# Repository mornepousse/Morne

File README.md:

The keyboard I created is a derivative of the Jorne and Kyria rev2, two keyboards highly appreciated in the community of mechanical keyboard enthusiasts. I took the best for me.

fr : Le clavier que j'ai créé est un dérivé du Jorne et du Kyria rev2, deux claviers très appréciés dans la communauté des amateurs de claviers mécaniques. J'ai pris le meilleur pour moi.

Update: 

Currently, I have not yet had the time to test the PCB and create the QMK code.

Actuellement, je n'ai pas encore eu le temps de tester le PCB et de créer le code QMK.

## PCB

Creation date: 02/12/2022

By ordering on [JLCPCB](https://cart.jlcpcb.com/quote?orderType=1&stencilLayer=2&stencilWidth=100&stencilLength=100&stencilCounts=5):

x 5 = 10.60$

u = 2.12$ x 2 = 4.24$

| Id | Reference | Package | Quantity | Designation | Supplier and ref | Ali price |
|----|-----------|---------|----------|------------|-------------------|------|
| 1  | D1,D2,D3...| Diode_TH_SOD123EKR | 26 | D |  [aliexpress](https://fr.aliexpress.com/item/1005003631407506.html?spm=a2g0o.order_list.order_list_main.10.6f255e5bMe6RnY&gatewayAdapt=glo2fra) , [TME](https://www.tme.eu/fr/details/1n5711w-7-f/diodes-schottky-smd/diodes-incorporated/) | 0.0546€ x 26 = 1.42€ |
| 2  | L1,L2,L3...| SK6812MINI_rev | 26 | SK6812MINI |  [aliexpress](https://fr.aliexpress.com/item/1005003021596311.html?spm=a2g0o.order_list.order_list_main.20.6f255e5bMe6RnY&gatewayAdapt=glo2fra) | 0.0704€ x 26 = 1.83€ |
| 3  | SW1,SW2,SW3...| MX_Socket_18mm | 26 | SW_PUSH | [aliexpress](https://fr.aliexpress.com/item/1005003873653184.html?spm=a2g0o.order_list.order_list_main.55.6f255e5bMe6RnY&gatewayAdapt=glo2fra)  | 0.1285€ x 26 = 3.34€ |
| 5  | U1 | ProMicro_v2 | 1 | ProMicro | [aliexpress](https://fr.aliexpress.com/item/1005003622414316.html?spm=a2g0o.order_list.order_list_main.26.6f255e5bMe6RnY&gatewayAdapt=glo2fra)  | 6.155€ |
| 8  | JP1 | JPC2 | 1 |  1X4Pin | [aliexpress](https://fr.aliexpress.com/item/4000979967513.html?spm=a2g0o.productlist.main.15.5b3f66e9o9m0cy&algo_pvid=850782ff-bfc7-4801-b06f-c64a524add1d&algo_exp_id=850782ff-bfc7-4801-b06f-c64a524add1d-7&pdp_ext_f=%7B%22sku_id%22%3A%2210000013144422246%22%7D&pdp_npi=3%40dis%21EUR%210.95%210.91%21%21%21%21%21%4021227e5116761981638552814d0652%2110000013144422246%21sea%21FR%212090266028&curPageLogUid=i54TIsZb6YSi)  | 0.182€ |
| 9  | J2 | OLED | 1 | OLED |  [aliexpress](https://fr.aliexpress.com/item/33024849277.html?spm=a2g0o.order_list.order_list_main.288.3e135e5bkwqkdx&gatewayAdapt=glo2fra) | 3.10€ |
| 10 | J1 | MJ-4PP-9 | 1 | MJ-4PP-9 |  [aliexpress](https://fr.aliexpress.com/item/33029465106.html?spm=a2g0o.order_list.order_list_main.253.3e135e5bkwqkdx&gatewayAdapt=glo2fra) | 0.246€ |
| 11 | RSW1 | ResetSW | 1 | SW_PUSH | [aliexpress](https://fr.aliexpress.com/item/1005004067514307.html?spm=a2g0o.productlist.main.1.73f16315tgnplA&algo_pvid=d4307642-89a4-423d-b78d-a7bb9a884aa8&algo_exp_id=d4307642-89a4-423d-b78d-a7bb9a884aa8-0&pdp_ext_f=%7B%22sku_id%22%3A%2212000027928467484%22%7D&pdp_npi=3%40dis%21EUR%210.52%210.46%21%21%21%21%21%40211bea0816761983658792786d0728%2112000027928467484%21sea%21FR%212090266028&curPageLogUid=7tFJg1Tj6lU0)  | 0.137€ |
| 12 | L22,L23,L24... | SK6812MINI_underglow_rev | 7 | SK6812MINI |  [aliexpress](https://fr.aliexpress.com/item/1005003021596311.html?spm=a2g0o.order_list.order_list_main.20.3e135e5bkwqkdx&gatewayAdapt=glo2fra) | 0.0704€ x 7 = 0.49€ |

Total price : 16.45€ x 2 = 32.90€

Other Parts:
| Name | links |
|------------------------|-----------------------------------------------|
| Jack TRRS cable | [ali1](https://fr.aliexpress.com/item/1005003415667083.html?spm=a2g0o.productlist.main.37.3441d84fbFu5Hf&algo_pvid=1adb3a47-ca94-434c-803d-4ccde599e237&algo_exp_id=1adb3a47-ca94-434c-803d-4ccde599e237-18&pdp_ext_f=%7B%22sku_id%22%3A%2212000025692890634%22%7D&pdp_npi=3%40dis%21EUR%212.14%211.81%21%21%21%21%21%4021227d8316762009574963433d0686%2112000025692890634%21sea%21FR%212090266028&curPageLogUid=nj2yMe0X7UII) [ali2](https://fr.aliexpress.com/item/33006667627.html?spm=a2g0o.productlist.main.25.3441d84fbFu5Hf&algo_pvid=db7c9240-7399-4f47-bad7-a78af453f498&algo_exp_id=db7c9240-7399-4f47-bad7-a78af453f498-12&pdp_ext_f=%7B%22sku_id%22%3A%2267037901505%22%7D&pdp_npi=3%40dis%21EUR%212.33%212.1%21%21%21%21%21%4021227e5116762010359954759d0652%2167037901505%21sea%21FR%212090266028&curPageLogUid=f0e0CcMaVshO) [ali3](https://fr.aliexpress.com/item/1005002888851426.html?spm=a2g0o.productlist.main.3.3441d84fbFu5Hf&algo_pvid=f9d24cf2-f17b-4ef0-a9a0-7f2f2ca77156&algo_exp_id=f9d24cf2-f17b-4ef0-a9a0-7f2f2ca77156-1&pdp_ext_f=%7B%22sku_id%22%3A%2212000022630947685%22%7D&pdp_npi=3%40dis%21EUR%213.8%212.66%21%21%21%21%21%40211bda9b16762013003935948d0706%2112000022630947685%21sea%21FR%212090266028&curPageLogUid=8BMH4jwvmLwd) |
| Switchs | [ali1](https://fr.aliexpress.com/item/1005003436102892.html?spm=a2g0o.order_list.order_list_main.223.34db5e5bkYd3Bk&gatewayAdapt=glo2fra), [ali Khail Cream](https://fr.aliexpress.com/item/1005003694230110.html?spm=a2g0o.productlist.main.1.5385245cS4FtLp&algo_pvid=043b18d1-9122-4b42-8289-2a2ee88619fe&algo_exp_id=043b18d1-9122-4b42-8289-2a2ee88619fe-0&pdp_ext_f=%7B%22sku_id%22%3A%2212000026831639163%22%7D&pdp_npi=3%40dis%21EUR%21177.39%2172.73%21%21%21%21%21%402102188b16762015218328204d070d%2112000026831639163%21sea%21FR%212090266028&curPageLogUid=lFpdV2qDqqbg) |
| Keycaps | [AF SA](https://fr.aliexpress.com/item/1005003935785708.html?spm=a2g0o.order_list.order_list_main.5.41db5e5b7Wn8vO&gatewayAdapt=glo2fra), [cerise](https://fr.aliexpress.com/item/1005003932690197.html?gatewayAdapt=glo2fra) |

Simulate the final price (case not included):

| PCB | SMDs | Switchs | Keycaps[?](https://fr.aliexpress.com/item/1005003935785708.html?spm=a2g0o.order_list.order_list_main.5.41db5e5b7Wn8vO&gatewayAdapt=glo2fra) | Total |
|----------|----------|----------|----------|----------|
| 3.97€ | 32.90€ | 18.06€ | 48.98€ | 103.91€ |

[BOM](https://github.com/mornepousse/Morne/blob/jorne/doc/BOM.md)

[Firmware](https://github.com/mornepousse/Rouge-Gorge_QMX_Part)

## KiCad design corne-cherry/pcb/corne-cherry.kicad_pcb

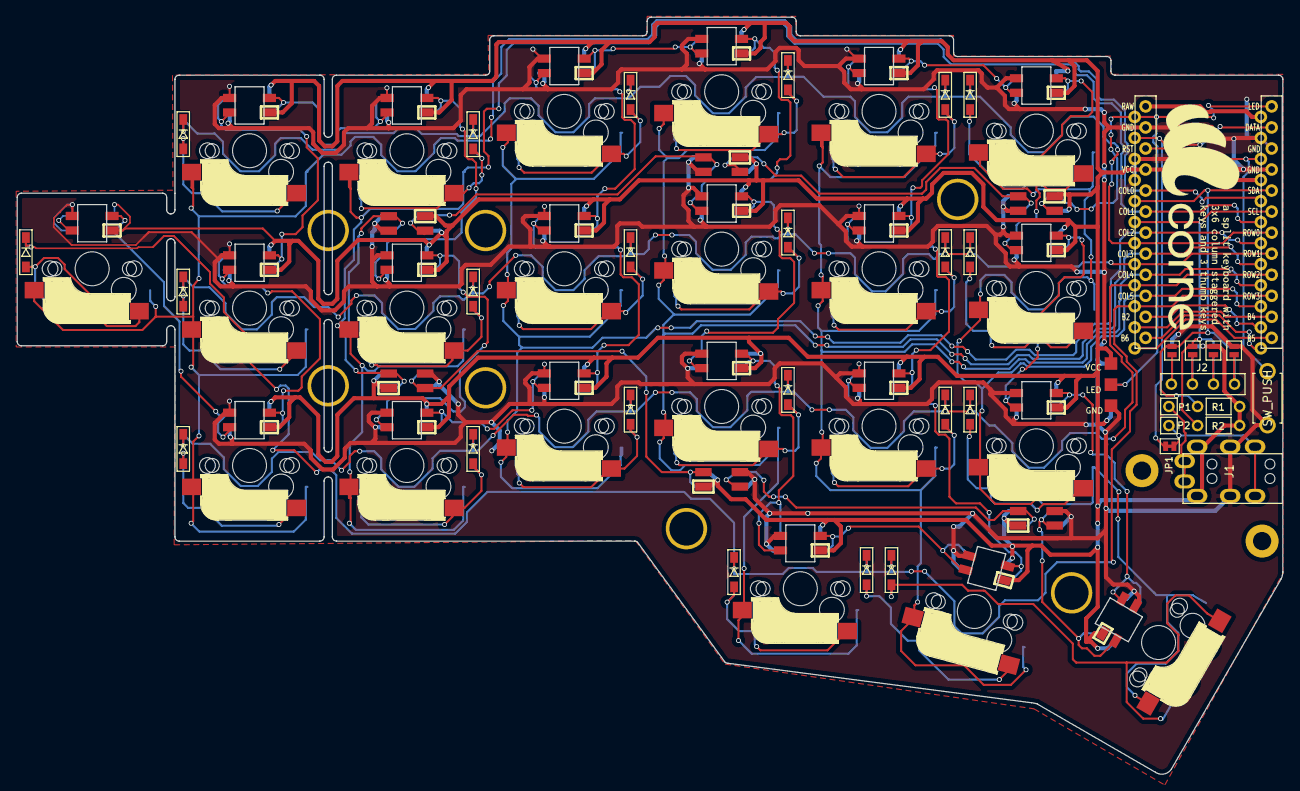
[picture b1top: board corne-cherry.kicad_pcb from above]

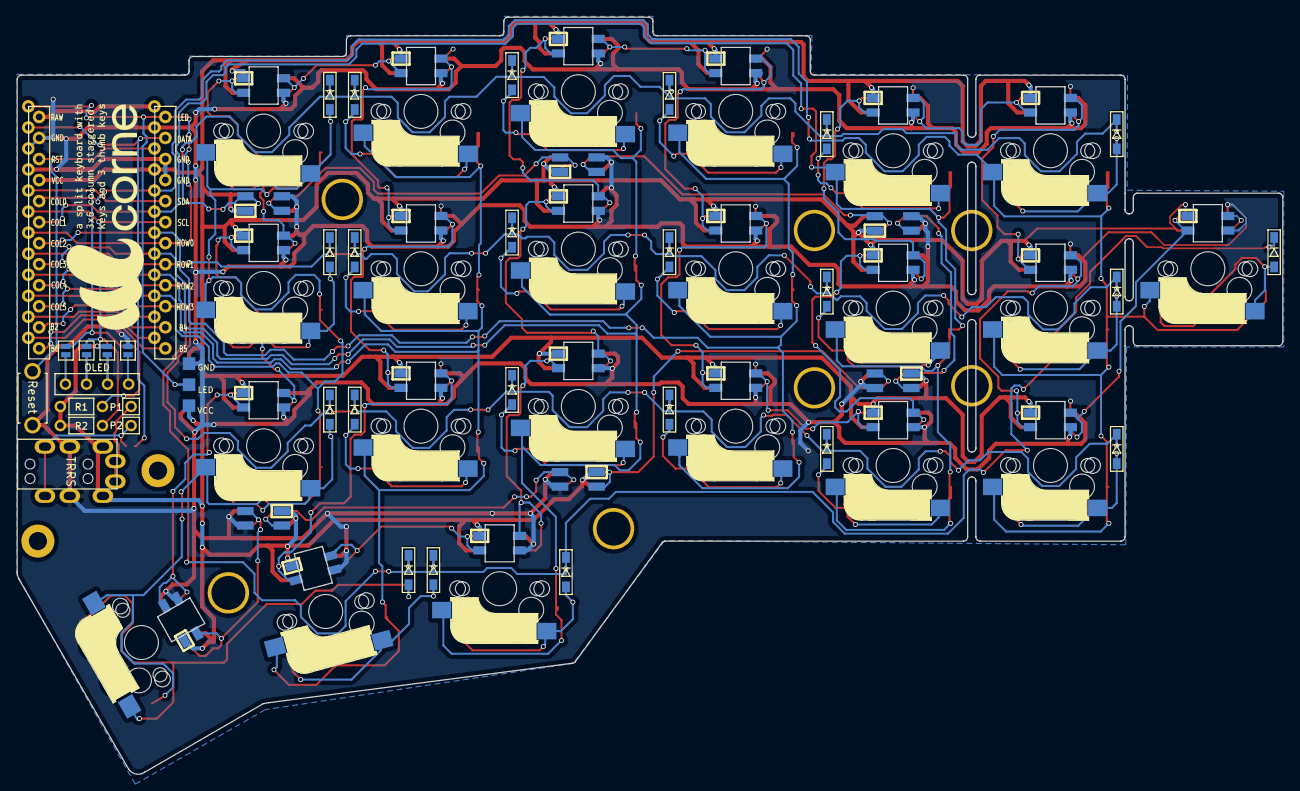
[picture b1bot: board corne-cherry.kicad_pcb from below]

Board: 2 copper layers, 152.8 x 91.4 mm, 101 parts (5 on the bottom side), 72 nets.

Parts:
D1, D2, D3, D4, D5, D6, D7, D8, D9, D10, D11, D12, D13, D14, D15, D16, D17, D18, D19, D20, D21, D22: D; D3_SMD
G01, G02: Logo_Open_Hardware_Small; corne
H1, H2, H3, H4, H5, H6, H7, H8, H9: MountingHole; LEGO_HOLE
J1: MJ-4PP-9
J2: OLED
J3: LED; StripLED_rev
JP1: JPC2
JP2, JP3, JP4, JP5, JP6, JP7, JP8, JP9: Jumper
L1, L2, L3, L4, L5, L6, L7, L8, L9, L10, L11, L12, L13, L14, L15, L16, L17, L18, L19, L20, L21, L28: SK6812MINI; SK6812MINI_rev
L22, L23, L24, L25, L26, L27: SK6812MINI; SK6812MINI_underglow_rev
P1, P2: i2c-pin; 1pin_conn
R1, R2: R
RSW1: SW_PUSH; ResetSW
SW1, SW2, SW3, SW4, SW5, SW6, SW7, SW8, SW9, SW10, SW11, SW12, SW13, SW14, SW15, SW16, SW17, SW18, SW19, SW20, SW22: SW_PUSH; CherryMX_MidHeight_Hotswap
SW21: SW_PUSH; CherryMX_MidHeight_Hotswap_1.5u
U1: ProMicro; ProMicro_v2

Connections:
GND: J1.C, J3.1, JP2.1, JP9.1, L1.2, L2.2, L3.2, L4.2, L5.2, L6.2, L7.2, L8.2, L9.2, L10.2, L11.2, L12.2, L13.2, L14.2, L15.2, L16.2, L17.2, L18.2, L19.2, L20.2, L21.2, L22.2, L23.2, L24.2, L25.2, L26.2, L27.2, L28.2, RSW1.2, U1.3, U1.4, U1.23
LED: J3.2, L24.3, U1.1
unnamed: D1.2, SW1.2
unnamed: D2.2, SW2.2
unnamed: D3.2, SW3.2
unnamed: D4.2, SW4.2
unnamed: D5.2, SW5.2
unnamed: D6.2, SW6.2
unnamed: D7.2, SW7.2
unnamed: D8.2, SW8.2
unnamed: D9.2, SW9.2
unnamed: D10.2, SW10.2
unnamed: D11.2, SW11.2
unnamed: D12.2, SW12.2
unnamed: D13.2, SW13.2
unnamed: D14.2, SW14.2
unnamed: D15.2, SW15.2
unnamed: D16.2, SW16.2
unnamed: D17.2, SW17.2
unnamed: D18.2, SW18.2
unnamed: D19.2, SW19.2
unnamed: D20.2, SW20.2
unnamed: D21.2, SW21.2
unnamed: D22.2, SW22.2
unnamed: J1.A, P1.1
unnamed: J1.B, JP1.2, P2.1
unnamed: J2.1, JP5.2, JP9.2
unnamed: J2.2, JP4.2, JP8.2
unnamed: J2.3, JP3.2, JP7.2
unnamed: J2.4, JP2.2, JP6.2
unnamed: L1.1, L7.3
unnamed: L1.3, L2.1
unnamed: L2.3, L8.1
unnamed: L3.1, L9.3
unnamed: L3.3, L4.1
unnamed: L5.3, L6.1
unnamed: L4.3, L10.1
unnamed: L10.3, L16.1
unnamed: L11.1, L17.3
unnamed: L5.1, L11.3
unnamed: L6.3, L12.1
unnamed: L12.3, L18.1
unnamed: L13.1, L28.3
unnamed: L7.1, L13.3
unnamed: L8.3, L14.1
unnamed: L14.3, L15.1
unnamed: L9.1, L15.3
unnamed: L16.3, L19.1
unnamed: L17.1, L20.3
unnamed: L18.3, L21.1
unnamed: L19.3, L20.1
unnamed: L21.3, L27.1
unnamed: L22.1, L25.3
unnamed: L22.3, L23.1
unnamed: L23.3, L24.1
unnamed: L25.1, L26.3
unnamed: L26.1, L27.3
SCL: JP4.1, JP7.1, R2.2, U1.6
SDA: JP5.1, JP6.1, R1.2, U1.5
VCC: J1.D, J3.3, JP3.1, JP8.1, L1.4, L2.4, L3.4, L4.4, L5.4, L6.4, L7.4, L8.4, L9.4, L10.4, L11.4, L12.4, L13.4, L14.4, L15.4, L16.4, L17.4, L18.4, L19.4, L20.4, L21.4, L22.4, L23.4, L24.4, L25.4, L26.4, L27.4, L28.4, R1.1, R2.1, U1.21
col0: SW1.1, SW7.1, SW13.1, SW22.1, U1.20
col1: SW2.1, SW8.1, SW14.1, U1.19
col2: SW3.1, SW9.1, SW15.1, U1.18
col3: SW4.1, SW10.1, SW16.1, SW19.1, U1.17
col4: SW5.1, SW11.1, SW17.1, SW20.1, U1.16
col5: SW6.1, SW12.1, SW18.1, SW21.1, U1.15
data: JP1.1, U1.2
reset: RSW1.1, U1.22
row0: D1.1, D2.1, D3.1, D4.1, D5.1, D6.1, U1.7
row1: D7.1, D8.1, D9.1, D10.1, D11.1, D12.1, U1.8
row2: D13.1, D14.1, D15.1, D16.1, D17.1, D18.1, U1.9
row3: D19.1, D20.1, D21.1, D22.1, U1.10

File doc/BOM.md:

Creation date: 02/12/2023


By ordering on [JLCPCB](https://cart.jlcpcb.com/quote?orderType=1&stencilLayer=2&ste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

x 5 = 10.60$

u = 2.12$ x 2 = 4.24$


| Id | Reference | Package | Quantity | Designation | Supplier and ref | Ali price |
|----|-----------|---------|----------|------------|-------------------|------|
| 1  | D1,D2,D3...| Diode_TH_SOD123EKR | 26 | D |  [aliexpress](https://fr.aliexpress.com/item/1005003631407506.html?spm=a2g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 , [TME](https://www.tme.eu/fr/details/1n5711w-7-f/diodes-schottky-sm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 | 0.0546€ x 26 = 1.42€ |
| 2  | L1,L2,L3...| SK6812MINI_rev | 26 | SK6812MINI |  [aliexpress](https://fr.aliexpress.com/item/1005003021596311.html?spm=a2g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 | 0.0704€ x 26 = 1.83€ |
| 3  | SW1,SW2,SW3...| MX_Socket_18mm | 26 | SW_PUSH | [aliexpress](https://fr.aliexpress.com/item/1005003873653184.html?spm=a2g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  | 0.1285€ x 26 = 3.34€ |
| 5  | U1 | ProMicro_v2 | 1 | ProMicro | [aliexpress](https://fr.aliexpress.com/item/1005003622414316.html?spm=a2g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  | 6.155€ |
| 8  | JP1 | JPC2 | 1 |  1X4Pin | [aliexpress](https://fr.aliexpress.com/item/4000979967513.html?spm=a2g0o.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  | 0.182€ |
| 9  | J2 | OLED | 1 | OLED |  [aliexpress](https://fr.aliexpress.com/item/33024849277.html?spm=a2g0o.or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 | 3.10€ |
| 10 | J1 | MJ-4PP-9 | 1 | MJ-4PP-9 |  [aliexpress](https://fr.aliexpress.com/item/33029465106.html?spm=a2g0o.or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 | 0.246€ |
| 11 | RSW1 | ResetSW | 1 | SW_PUSH | [aliexpress](https://fr.aliexpress.com/item/1005004067514307.html?spm=a2g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  | 0.137€ |
| 12 | L22,L23,L24... | SK6812MINI_underglow_rev | 7 | SK6812MINI |  [aliexpress](https://fr.aliexpress.com/item/1005003021596311.html?spm=a2g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 | 0.0704€ x 7 = 0.49€ |


Total price : 16.45€ x 2 = 32.90€

Other Parts :
| Name | links |
|------------------------|-----------------------------------------------|
| Jack TRRS cable | [ali1](https://fr.aliexpress.com/item/1005003415667083.html?spm=a2g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 [ali2](https://fr.aliexpress.com/item/33006667627.html?spm=a2g0o.pr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 [ali3](https://fr.aliexpress.com/item/1005002888851426.html?spm=a2g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 |
| Switchs | [ali1](https://fr.aliexpress.com/item/1005003436102892.html?spm=a2g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, [ali Khail Cream](https://fr.aliexpress.com/item/1005003694230110.html?spm=a2g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 |

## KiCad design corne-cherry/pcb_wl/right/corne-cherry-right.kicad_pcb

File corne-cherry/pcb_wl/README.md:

# Jorne WL keyboard

This revision is based on the Corne V3 and is optimised for wireless use.

- LEDs are removed
- Supports MX/Alps/MX hotswap
- Uses MSK12C01 power switches (outward is off, inward is on)
- Has through-hole battery contacts (square is ground, circle is RAW)
- Battery contacts are wired through the power switch
- Pinky keys can be broken off

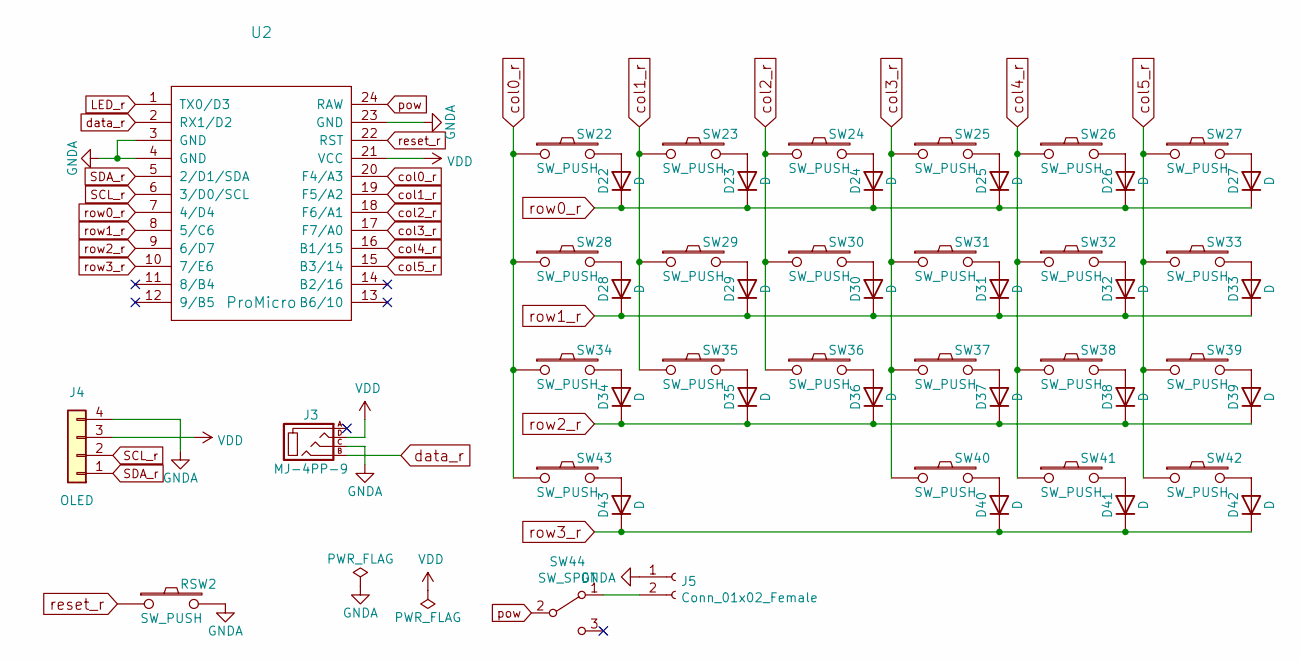
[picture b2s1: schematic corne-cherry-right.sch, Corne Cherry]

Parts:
D22, D23, D24, D25, D26, D27, D28, D29, D30, D31, D32, D33, D34, D35, D36, D37, D38, D39, D40, D41, D42, D43: D; D3_SMD_v2
J3: MJ-4PP-9; MJ-4PP-9_1side
J4: OLED; OLED_1side
J5: Conn_01x02_Female; PinHeader_1x02_P2.00mm_Vertical
RSW2: SW_PUSH; ResetSW_1side
SW22, SW23, SW24, SW25, SW26, SW27, SW28, SW29, SW30, SW31, SW32, SW33, SW34, SW35, SW36, SW37, SW38, SW39, SW40, SW41, SW43: SW_PUSH; CherryMX_Hotswap
SW42: SW_PUSH; CherryMX_Hotswap_1.5u
SW44: SW_SPDT; SW_SPDT+H-MSK12C01_hor(7pin_SMD)
U2: ProMicro; ProMicro_v3

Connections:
GNDA: J3.C, J4.4, J5.1, RSW2.2, U2.3 (GND), U2.4 (GND), U2.23 (GND)
LED_r: U2.1 (TX0/D3)
unnamed: D22.2 (A), SW22.2
unnamed: D23.2 (A), SW23.2
unnamed: D24.2 (A), SW24.2
unnamed: D25.2 (A), SW25.2
unnamed: D26.2 (A), SW26.2
unnamed: D27.2 (A), SW27.2
unnamed: D28.2 (A), SW28.2
unnamed: D29.2 (A), SW29.2
unnamed: D30.2 (A), SW30.2
unnamed: D31.2 (A), SW31.2
unnamed: D32.2 (A), SW32.2
unnamed: D33.2 (A), SW33.2
unnamed: D34.2 (A), SW34.2
unnamed: D35.2 (A), SW35.2
unnamed: D36.2 (A), SW36.2
unnamed: D37.2 (A), SW37.2
unnamed: D38.2 (A), SW38.2
unnamed: D39.2 (A), SW39.2
unnamed: D40.2 (A), SW40.2
unnamed: D41.2 (A), SW41.2
unnamed: D42.2 (A), SW42.2
unnamed: D43.2 (A), SW43.2
unnamed: J5.2, SW44.1 (A)
SCL_r: J4.2, U2.6 (3/D0/SCL)
SDA_r: J4.1, U2.5 (2/D1/SDA)
VDD: J3.D, J4.3, U2.21 (VCC)
col0_r: SW22.1, SW28.1, SW34.1, SW43.1, U2.20 (F4/A3)
col1_r: SW23.1, SW29.1, SW35.1, U2.19 (F5/A2)
col2_r: SW24.1, SW30.1, SW36.1, U2.18 (F6/A1)
col3_r: SW25.1, SW31.1, SW37.1, SW40.1, U2.17 (F7/A0)
col4_r: SW26.1, SW32.1, SW38.1, SW41.1, U2.16 (B1/15)
col5_r: SW27.1, SW33.1, SW39.1, SW42.1, U2.15 (B3/14)
data_r: J3.B, U2.2 (RX1/D2)
pow: SW44.2 (B), U2.24 (RAW)
reset_r: RSW2.1, U2.22 (RST)
row0_r: D22.1 (K), D23.1 (K), D24.1 (K), D25.1 (K), D26.1 (K), D27.1 (K), U2.7 (4/D4)
row1_r: D28.1 (K), D29.1 (K), D30.1 (K), D31.1 (K), D32.1 (K), D33.1 (K), U2.8 (5/C6)
row2_r: D34.1 (K), D35.1 (K), D36.1 (K), D37.1 (K), D38.1 (K), D39.1 (K), U2.9 (6/D7)
row3_r: D40.1 (K), D41.1 (K), D42.1 (K), D43.1 (K), U2.10 (7/E6)

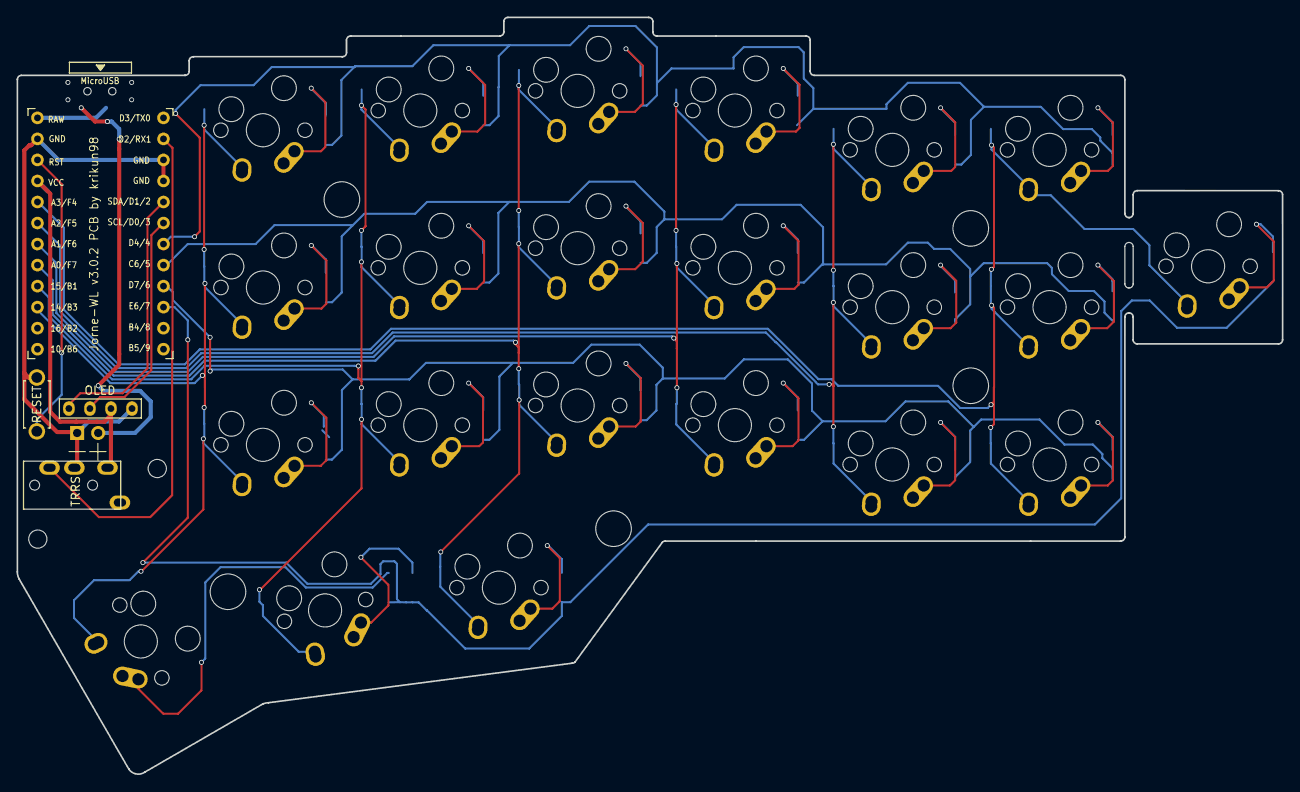
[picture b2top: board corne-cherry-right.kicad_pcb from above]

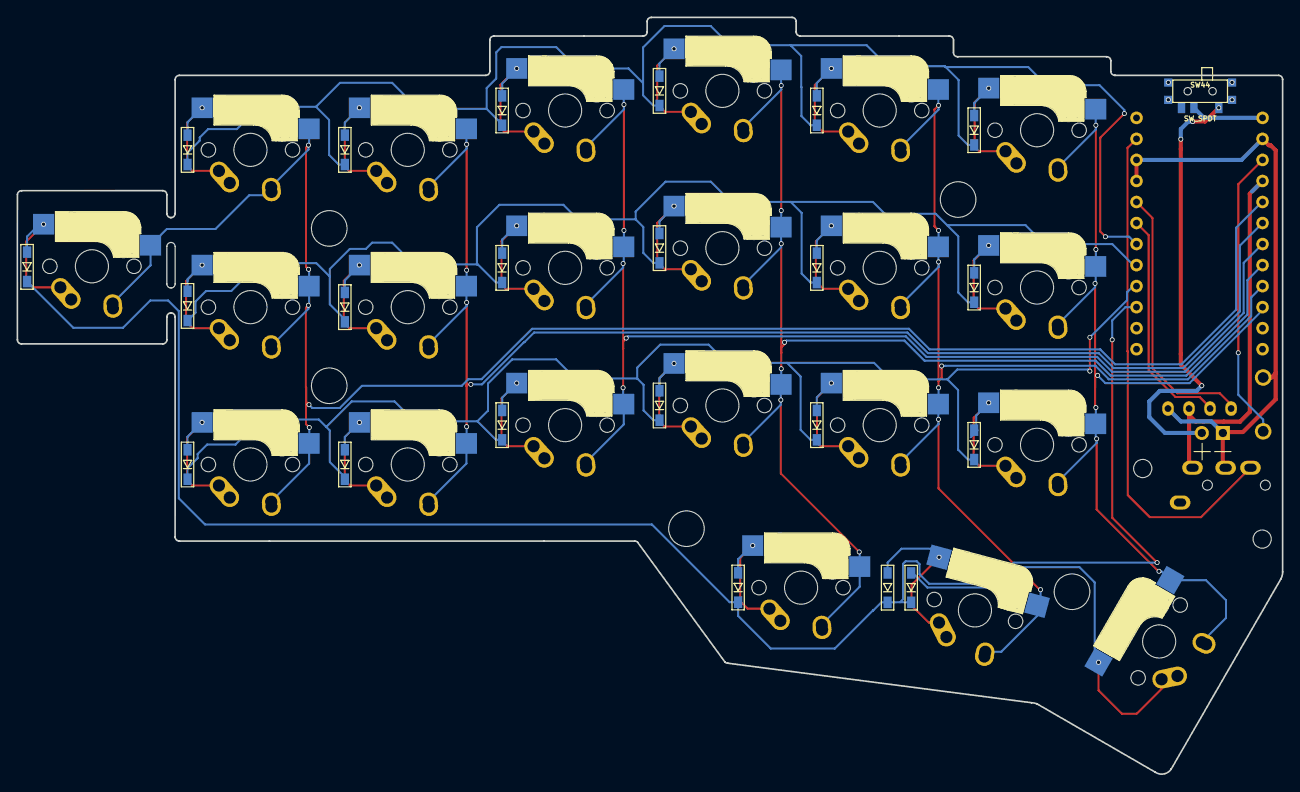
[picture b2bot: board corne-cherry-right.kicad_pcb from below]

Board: 2 copper layers, 152.8 x 91.4 mm, 57 parts (26 on the bottom side), 40 nets.

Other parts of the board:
Ref**: Val**; M2_HOLE_v2
Ref**#2, Ref**#3, Ref**#4, Ref**#5, Ref**#6, Ref**#7: Val**; M2_HOLE_v2

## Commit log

2019-07-12 fixed download link
2019-07-12 fixed download link 2
2019-07-12 fixed typo
2019-07-14 fixed corne-cherry outlines
2019-07-14 added warning
2019-07-14 added zones, fixed silk
2019-07-14 fixed schematic
2019-07-14 added gerbers and download links
2019-07-14 fixed download links
2019-07-14 renamed to 2.0 to avoid confusion
2019-07-14 added modification section
2019-08-15 added images
2019-08-15 added drawings
2019-08-15 updated drawings
2019-08-15 fixed links
2019-08-17 updated dxf
2019-08-17 added quote
2019-08-18 added nrfmicro version
2019-08-18 updated nrfmicro
2019-08-18 added classic-nrfmicro
2019-08-18 updated gerbers
2019-08-20 added warning about jlcpcb
2019-08-21 removed combined boards because jlcpcb sucks
2019-08-21 deleted images
2019-08-21 updated corne-cherry
2019-08-21 added new embedded promicros
2019-08-21 updated jorne-classic-2.1
2019-08-24 added metal plate
2019-08-24 added files
2019-08-27 added BOM
2019-08-27 added tilting-tenting-jorne-half
2019-08-27 updated files
2019-08-27 fixed jorne-simple.dxf
2019-08-28 fixed dxf
2019-09-10 added firmware
2019-09-16 fixed LED holes in corne-cherry 2.1
2019-09-17 removed link to nrfmicro gerbers
2019-09-17 removed nrfmicro gerber (no led hole)
2019-09-24 added steel plates with 14.00 mm cutouts
2019-11-29 updated jorne-simple.dxf
2020-01-07 added PCB top plate
2020-01-07 added gerbers
2020-01-07 added image
2020-01-08 added bottom plate
2020-01-08 updated jorne-tilted.dxf, added pictures
2020-07-10 added case.stl
2020-07-16 added stl and stp files
2020-07-24 removed old stl
2020-10-17 Added jorne-cherry-3.0
2020-11-15 Update README.md
    add 3D print case
2020-12-15 added jorne.blend
2020-12-16 fixed units
2020-12-16 fixed outlines for pcb plates
2020-12-18 fixed geometry
2020-12-18 fixed cutouts (note halves are asymmetrical!)
2020-12-18 fixed non-manifold
2020-12-19 3d case released, left and right halves
2020-12-19 fixed tab size of the pinky key
2021-07-19 Added Jorne Wireless PCB files
2021-07-19 Added top and bottom plates with breakoff pinkies to match the Jorne-WL PCB
2021-07-30 Bug fixes and other minor improvements
2021-08-24 Two solder pads for 'p' and ';' were unrouted
2021-08-29 added plated plate
2021-10-03 Small revision bump: bigger battery header, smaller footprints
2021-12-27 added jorne hi-pro m5 with tenting
2022-12-03 Clean
    Clean up
2022-12-03 V1 morne
2022-12-03 add image
2022-12-03 add logo
2022-12-03 edit logo
2022-12-04 v.1.0
2023-02-12 Add DOM file
2023-02-12 Addition of the preliminary BOM
2023-02-12 Add Simulate the final price (case not included)
2023-02-12 add keycaps in BOM.md
2023-02-20 add test logo
2023-02-22 Add and remove images
2023-02-22 Add PCB image
2023-03-02 Correction Led - new Logo
2023-03-02 Add image image first build
2023-07-31 Update README.md
    oups
2023-08-20 Update README.md
    Add firmware link
